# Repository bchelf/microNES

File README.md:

# microNES

`microNES` is a small RP2350-based NES emulator project with custom hardware,
portable emulator code, and host-side development tools.

The repo now includes a complete KiCad implementation of an RP2350 console-style
board, plus firmware for composite video, HDMI output, SD-card ROM loading,
controller input, and audio. It also includes host tools for building, running,
capturing, and validating the same emulator core on a desktop.

ROM images are not included.

## What This Repo Does

- Runs NES ROMs through a shared C emulator core.
- Targets RP2350 / Raspberry Pi Pico 2-class hardware.
- Provides a fully functional KiCad PCB design under `hardware/microNES_pcb_v0.1`.
- Outputs analog composite video from the RP2350 using PIO/DMA timing.
- Outputs HDMI/DVI-style video using the RP2350 HSTX path.
- Loads ROMs at runtime from SD card, with an optional flash/XIP cache.
- Supports NES controller input.
- Produces audio through PWM on the Pico targets, with a MAX98357 I2S path for
  the TFT audio target.
- Builds host tools for smoke tests, SDL play, PNG frame dumps, WAV dumps, and
  ffmpeg video capture.
- Includes an ESP32-S3 frontend as a separate reference platform.
- Includes an Emscripten/WebAssembly target stub for browser experiments.

## Current Status

The project has moved beyond the original SMB1-only bring-up. The core still
prioritizes pragmatic compatibility over perfect NES accuracy, but the repo now
contains support for several common mapper families:

- NROM / mapper 0
- MMC1
- UxROM
- CNROM
- AxROM
- GxROM
- Color Dreams
- MMC2
- MMC3
- mapper 40

The hardware and firmware path is centered on the RP2350 board in
`hardware/microNES_pcb_v0.1`, with composite and HDMI firmware targets in
`src/pico`. The host path remains the fastest way to validate emulator behavior
before testing on hardware.

## Hardware

The KiCad project lives here:

```text
hardware/microNES_pcb_v0.1/
```

It includes:

- KiCad schematic and PCB files
- custom symbols and footprints
- RP2350 QFN footprint and 3D model support
- microSD slot support
- USB-C support
- NES controller connector footprint
- custom KiCad footprints for original Nintendo console parts
- composite output hardware
- production outputs, BOM, placement files, and Gerbers

The board is designed around harvested original NES console hardware for the
user-facing controls and controller interface. It uses the original Nintendo
power switch assembly and original NES controller input ports, with custom KiCad
footprints made specifically for those salvaged parts.

The older breadboard composite schematic is documented in `SCHEMATIC.md`. The
PCB target is selected in firmware with:

```sh
-DMICRONES_BOARD=v0_1
```

## Repo Layout

```text
src/common/      Portable emulator core, ROM menu, mappers, CPU, PPU, APU, input
src/host/        Desktop smoke runner, SDL runner, PNG/WAV/video tooling
src/pico/        RP2350 firmware, composite, HDMI, TFT, SD, flash cache, audio
src/esp32s3/     Separate ESP32-S3 frontend/reference implementation
src/web/         Emscripten/WebAssembly browser frontend
hardware/        KiCad PCB design, production files, Gerbers, BOMs
tests/           Emulator test ROMs and menu smoke tests
```

## Build

### Host

```sh
cmake -S . -B build-host -DMICRONES_PLATFORM=host
cmake --build build-host -j
```

This builds:

- `build-host/micrones_smoke`
- `build-host/micrones_menu_smoke`
- `build-host/micrones` when SDL3 is available

Run a ROM locally:

```sh
./build-host/micrones roms/smb1.nes
```

Run deterministic smoke validation:

```sh
./build-host/micrones_smoke roms/smb1.nes
```

Capture a frame or video:

```sh
./build-host/micrones_smoke roms/smb1.nes 6200000 /tmp/micrones_10s.png
./build-host/micrones_smoke roms/smb1.nes --steps 17670500 --video-out build-host/capture.mp4
```

### RP2350 / Pico

Configure the firmware for the emulator and the custom PCB:

```sh
cmake -S . -B build-pico \
  -DMICRONES_PLATFORM=pico \
  -DMICRONES_PICO_VIDEO_MODE=emulator \
  -DMICRONES_BOARD=v0_1 \
  -Dpicotool_DIR=/Users/bchelf/microNES/build/_deps/picotool
```

Build composite output:

```sh
cmake --build build-pico --target micrones_pico_analog -j
```

Build HDMI output:

```sh
cmake --build build-pico --target micrones_pico_hdmi -j
```

Other firmware targets:

```sh
cmake --build build-pico --target micrones_pico_tft -j
cmake --build build-pico --target micrones_pico_tft_max98357 -j
cmake --build build-pico --target micrones_pico_hdmi_test_pattern -j
```

The Pico firmware loads ROMs from SD at runtime. `MICRONES_PICO_ROM_PATH` is no
longer needed for normal Pico builds.

### Web

```sh
emcmake cmake -S . -B build-web -DMICRONES_PLATFORM=web
cmake --build build-web -j
```

The build copies `src/web/index.html` next to the generated JS/WASM output.

### ESP32-S3

```sh
cd src/esp32s3
. $IDF_PATH/export.sh
idf.py build
```

## Host Controls

For the SDL runner:

- Arrow keys or `WASD`: D-pad
- `L`: A
- `K`: B
- `Return`: Start
- `Tab` or right shift: Select

Useful runner options:

```sh
./build-host/micrones roms/smb1.nes --vsync
./build-host/micrones roms/smb1.nes --no-vsync --unthrottled
./build-host/micrones roms/smb1.nes --scale 5
./build-host/micrones roms/smb1.nes --dump-wav /tmp/gameplay.wav --dump-wav-seconds 2
```

## Known Limitations

`microNES` is still an emulator under active development, not a fully accurate
general-purpose NES implementation.

- PPU timing is practical rather than fully cycle-accurate.
- Sprite overflow and exact secondary OAM behavior are incomplete.
- APU fidelity is improved but still not perfect.
- Mapper support exists for several common boards, but compatibility is not
  expected to match mature NES emulators.
- Some RP2350 SD-to-flash-cache ROM load paths can still disturb video output
  and are an active debugging area.

## Development Notes

Keep platform boundaries clean:

- `src/common` should stay portable.
- Host-only SDL, PNG, WAV, and ffmpeg code belongs in `src/host`.
- Pico SDK, PIO, DMA, HSTX, SD, and flash code belongs in `src/pico`.
- ESP-IDF code belongs in `src/esp32s3`.

The recommended workflow is still host-first: validate behavior with
`micrones_smoke` and the SDL runner, then test the same core on RP2350 hardware.

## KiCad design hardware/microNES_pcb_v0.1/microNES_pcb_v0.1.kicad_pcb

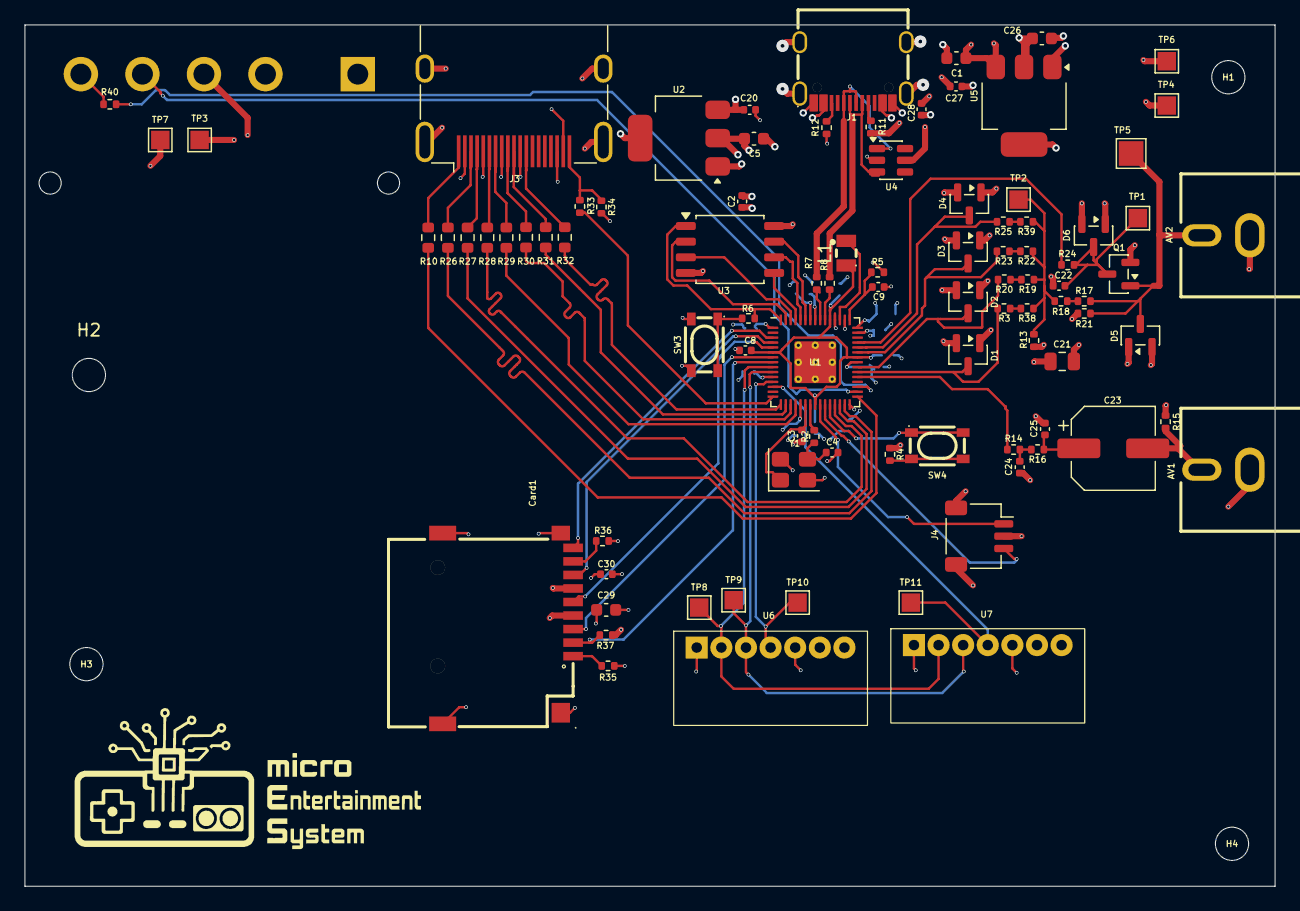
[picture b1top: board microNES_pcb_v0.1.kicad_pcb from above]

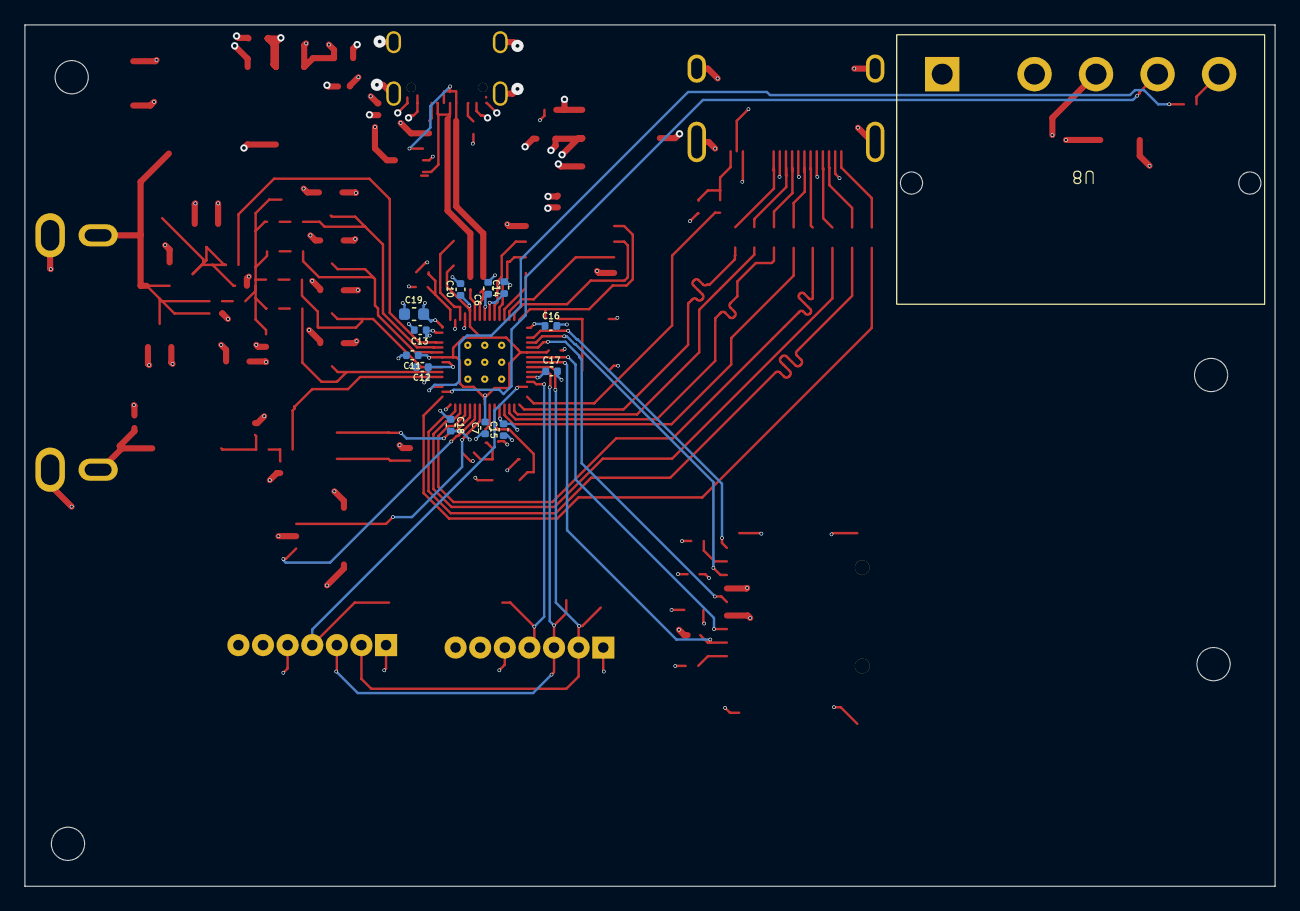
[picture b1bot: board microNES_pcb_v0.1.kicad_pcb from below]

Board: 4 copper layers, 101.6 x 70.0 mm, 108 parts (13 on the bottom side), 77 nets.

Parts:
AV1, AV2: AV-5; CONN-TH_AV-5
C1, C5, C19, C26, C29: 10uF; C_0603_1608Metric
C2, C8, C11, C12, C13, C14, C15, C16, C17, C18, C20, C27, C28, C30: 100nF; C_0402_1005Metric
C3, C4: 15pF; C_0402_1005Metric
C6, C7, C9, C10: 4.7uF; C_0402_1005Metric
C21: 100nF; C_0805_2012Metric
C22, C24, C25: 10nF; C_0402_1005Metric
C23: 100uF; CP_Elec_6.3x5.4
Card1: TF PUSH; TF-SMD_TF-PUSH
D1, D2, D3, D4, D5, D6: BAT54S; SOT-23
H1, H2, H3, H4: MountingHole; MountingHole_2.7mm_M2.5
J1: USB_C_Receptacle_USB2.0_16P; USB-C_SMD-TYPE-C-31-M-12_1
J3: HDMI_E; HDMI_A_Molex_208658-1001_Horizontal
J4: SM03B-SRSS-TB; JST_SH_SM03B-SRSS-TB_1x03-1MP_P1.00mm_Horizontal
L1: 3.3uH; IND-SMD_L2.0-W1.6_AOTA-B201610S3R3-101-T
Q1: 2N7002; SOT-23
R2, R3, R4, R6, R14, R16: 1k; R_0402_1005Metric
R5: 33; R_0402_1005Metric
R7, R8: 27; R_0402_1005Metric
R10, R26, R27, R28, R29, R30, R31, R32: 270; R_0603_1608Metric
R11, R12: 5.1k; R_0402_1005Metric
R13, R40: 330; R_0402_1005Metric
R15, R21, R33, R35, R36, R37: 10k; R_0402_1005Metric
R17: 7.5; R_0402_1005Metric
R18: 68; R_0402_1005Metric
R19: 15; R_0402_1005Metric
R20: 470; R_0402_1005Metric
R22: 22; R_0402_1005Metric
R23: 220; R_0402_1005Metric
R24: 100; R_0402_1005Metric
R25: 120; R_0402_1005Metric
R34: 20k; R_0402_1005Metric
R38, R39: 0; R_0402_1005Metric
SW3, SW4: PTS810SJM250SMTRLFS; KEY-SMD_4P-L4.2-W3.2-P2.20-LS4.6
TP1: TestPoint; TestPoint_Pad_1.5x1.5mm
TP2, TP3, TP4, TP6, TP7, TP8, TP9, TP10, TP11: TestPoint_Pad_1.5x1.5mm
TP5: TestPoint; TestPoint_Pad_2.0x2.0mm
U1: RP2350_60QFN; RP2350-QFN-60-1EP_7x7_P0.4mm_EP3.4x3.4mm_ThermalVias
U2, U5: AMS1117-3.3; SOT-223-3_TabPin2
U3: W25Q128JVS; SOIC-8_5.3x5.3mm_P1.27mm
U4: SOT-23-6
U6, U7: NES_1x7_CustomPitch
U8: NES_Power_Reset_LED_5pin
Y1: ABM8-272-T3; Crystal_SMD_3225-4Pin_3.2x2.5mm

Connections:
+1V1: C7.1, C8.1, C10.1, C11.1, L1.1, U1.6 (DVDD), U1.23 (DVDD), U1.39 (DVDD), U1.50 (VREG_FB)
+3.3VDAC: C21.1, C26.1, D1.2 (K), D2.2 (K), D3.2 (K), D4.2 (K), D5.2 (K), D6.2 (K), R13.1, TP6.1 (1_1), U5.2 (VO)
+3V3: C2.1, C5.1, C6.1, C12.1, C13.1, C14.1, C15.1, C16.1, C17.1, C18.1, C19.1, C29.1, C30.1, Card1.4 (VDD), R5.1, R35.1, R36.1, R37.1, TP3.1 (1_1), U1.1 (IOVDD), U1.11 (IOVDD), U1.20 (IOVDD), U1.30 (IOVDD), U1.38 (IOVDD), U1.44 (ADC_AVDD), U1.45 (IOVDD), U1.49 (VREG_VIN), U1.53 (USB_OTP_VDD), U1.54 (QSPI_IOVDD), U2.2 (VO), U3.8 (VCC), U6.5 (VCC), U7.5 (VCC), U8.3 (RST_VCC)
/ADAC_OUT: AV1.2, C23.2, R15.1
/AUD_A: C24.1, R14.2, R16.1
/AUD_B: C23.1, C25.1, R16.2
/CARD_CD: Card1.CD, U1.3 (GPIO1)
/CARD_CD_DAT3: Card1.2 (CD/DAT3), R37.2, U1.8 (GPIO5)
/CARD_CLX: Card1.5 (CLX), U1.5 (GPIO3)
/CARD_CMD: Card1.3 (CMD), U1.7 (GPIO4)
/CARD_DAT0: Card1.7 (DAT0), U1.4 (GPIO2)
/GATE_NODE: C22.1, D6.3 (COM), Q1.3 (D), R24.1, TP1.1 (1_1)
/GPIO12: R32.1, U1.16 (GPIO12)
/GPIO13: R31.1, U1.17 (GPIO13)
/GPIO14: R30.1, U1.18 (GPIO14)
/GPIO15: R29.1, U1.19 (GPIO15)
/GPIO16: R28.1, U1.27 (GPIO16)
/GPIO17: R27.1, U1.28 (GPIO17)
/GPIO18: R26.1, U1.29 (GPIO18)
/GPIO19: R10.1, U1.31 (GPIO19)
/GP_ADAC_IN: R14.1, U1.35 (GPIO23)
/GP_VDAC_GATE: R24.2, U1.42 (GPIO28_ADC2)
/GP_VDAC_SUM0: D1.3 (COM), R3.2, U1.36 (GPIO24)
/GP_VDAC_SUM1: D2.3 (COM), R20.2, U1.37 (GPIO25)
/GP_VDAC_SUM2: D3.3 (COM), R23.2, U1.40 (GPIO26_ADC0)
/GP_VDAC_SUM3: D4.3 (COM), R25.2, U1.41 (GPIO27_ADC1)
/HDMI_HPD: R33.2, U1.15 (GPIO11)
/NES_CLOCK: TP8.1 (1_1), U1.9 (GPIO6), U6.2 (CLOCK), U7.2 (CLOCK)
/NES_DATA_1: TP10.1 (1_1), U1.12 (GPIO8), U6.4 (DATA)
/NES_DATA_2: TP11.1 (1_1), U1.13 (GPIO9), U7.4 (DATA)
/NES_LATCH: TP9.1 (1_1), U1.10 (GPIO7), U6.3 (LATCH), U7.3 (LATCH)
/PWR_LED: R40.2, U1.33 (GPIO21)
/QSPI_SCLK: U1.56 (QSPI_SCLK), U3.6 (CLK)
/QSPI_SD0: U1.57 (QSPI_SD0), U3.5 (DI(IO0))
/QSPI_SD1: U1.59 (QSPI_SD1), U3.2 (DO(IO1))
/QSPI_SD2: U1.58 (QSPI_SD2), U3.3 (IO2)
/QSPI_SD3: U1.55 (QSPI_SD3), U3.7 (IO3)
/QSPI_SS: R6.1, U1.60 (QSPI_SS), U3.1 (~CS)
/RST_BTN: U1.32 (GPIO20), U8.4 (RST_OUT)
/RUN: SW4.1, SW4.2, U1.26 (RUN)
/SUM_NODE: R13.2, R18.2, R19.1, R22.1, R38.2, R39.2, TP2.1 (1_1)
/SWCLK: J4.1, U1.24 (SWCLK)
/SWD: J4.3, U1.25 (SWD)
/USB_D+: J1.A6 (DP1), J1.B6 (DP2), R7.1, U4.1 (IO1)
/USB_D-: J1.A7 (DN1), J1.B7 (DN2), R8.1, U4.3 (IO2)
/VBUS_RAW: J1.A4B9 (VBUS), J1.B4A9 (VBUS), U8.1 (PWR_SW_A)
/VDAC_OUT: AV2.2, D5.3 (COM), Q1.1 (G), R17.1, R21.2, TP5.1 (1_1)
/VREG_AVDD: C9.1, R5.2, U1.46 (VREG_AVDD)
/VREG_LX: L1.2, U1.48 (VREG_LX)
/XIN: C3.1, U1.21 (XIN), Y1.1
/XOUT: R2.1, U1.22 (XOUT)
/~USB_BOOT: R6.2, SW3.1, SW3.2
GND: AV1.1, AV2.1, C1.1, C2.2, C3.2, C4.2, C5.2, C6.2, C7.2, C8.2, C9.2, C10.2, C11.2, C12.2, C13.2, C14.2, C15.2, C16.2, C17.2, C18.2, C19.2, C20.1, C21.2, C22.2, C24.2, C25.2, C26.2, C27.1, C28.1, C29.2, C30.2, Card1.6 (VSS), Card1.10, Card1.11, Card1.12, Card1.13, D1.1 (A), D2.1 (A), D3.1 (A), D4.1 (A), D5.1 (A), D6.1 (A), J1.1 (EH), J1.2 (EH), J1.3 (EH), J1.4 (EH), J1.A1B12 (GND), J1.B1A12 (GND), J3.2 (D2S), J3.5 (D1S), J3.8 (D0S), J3.11 (CKS), J3.17 (GND), J3.SH, J4.2, J4.MP (MountPin), Q1.2 (S), R4.2, R11.1, R12.2, R15.2, R21.1, R34.2, SW3.3, SW3.4, TP4.1 (1_1), TP7.1 (1_1), U1.47 (VREG_PGND), U1.61 (GND), U2.1 (GND), U3.4 (GND), U4.2 (GND), U5.1 (GND), U6.1 (GND), U7.1 (GND), Y1.2, Y1.4
unnamed: C4.1, R2.2, Y1.3
unnamed: Card1.8 (DAT1), R36.2
unnamed: Card1.1 (DAT2), R35.2
unnamed: J1.A5 (CC1), R11.2
unnamed: J1.B5 (CC2), R12.1
unnamed: J3.10 (CK+), R31.2
unnamed: J3.12 (CK-), R32.2
unnamed: J3.7 (D0+), R29.2
unnamed: J3.9 (D0-), R30.2
unnamed: J3.4 (D1+), R27.2
unnamed: J3.6 (D1-), R28.2
unnamed: J3.1 (D2+), R10.2
unnamed: J3.3 (D2-), R26.2
unnamed: J3.19 (HPD), R33.1, R34.1
unnamed: R3.1, R38.1
unnamed: R4.1, SW4.3, SW4.4
unnamed: R17.2, R18.1
unnamed: R19.2, R20.1
unnamed: R22.2, R23.1
unnamed: R25.1, R39.1
unnamed: R8.2, U1.51 (USB_DM)
unnamed: R7.2, U1.52 (USB_DP)
unnamed: R40.1, U8.5 (LED_K)
VBUS: C1.2, C20.2, C27.2, C28.2, J3.18 (+5V), U2.3 (VI), U4.5 (VBUS), U5.3 (VI), U8.2 (PWR_SW_B)

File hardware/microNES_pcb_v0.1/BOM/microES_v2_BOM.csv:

Comment,Designator,Footprint,JLCPCB Part #
AV-5,"AV1,AV2",microNES_footprints:CONN-TH_AV-5,C18080
10uF,"C1,C5,C19,C26,C29",Capacitor_SMD:C_0603_1608Metric,C19702
100nF,"C2,C8,C11,C12,C13,C14,C15,C16,C17,C18,C20,C27,C28,C30",Capacitor_SMD:C_0402_1005Metric,C307331
15pF,"C3,C4",Capacitor_SMD:C_0402_1005Metric,C1548
4.7uF,"C6,C7,C9,C10",Capacitor_SMD:C_0402_1005Metric,C23733
100nF,C21,Capacitor_SMD:C_0805_2012Metric,C49678
10nF,"C22,C24,C25",Capacitor_SMD:C_0402_1005Metric,C15195
100uF,C23,Capacitor_SMD:CP_Elec_6.3x5.4,C29179
TF PUSH,Card1,microNES_footprints:TF-SMD_TF-PUSH,C393941
BAT54S,"D1,D2,D3,D4,D5,D6",Package_TO_SOT_SMD:SOT-23,C47546
USB_C_Receptacle_USB2.0_16P,J1,microNES_footprints:USB-C_SMD-TYPE-C-31-M-12_1,C165948
HDMI_E,J3,Connector_Video:HDMI_A_Molex_208658-1001_Horizontal,C2962407
SM03B-SRSS-TB,J4,Connector_JST:JST_SH_SM03B-SRSS-TB_1x03-1MP_P1.00mm_Horizontal,C160403
3.3uH,L1,microNES_footprints:IND-SMD_L2.0-W1.6_AOTA-B201610S3R3-101-T,C42411119
2N7002,Q1,Package_TO_SOT_SMD:SOT-23,C8545
1k,"R2,R3,R4,R6,R14,R16",Resistor_SMD:R_0402_1005Metric,C11702
33,R5,Resistor_SMD:R_0402_1005Metric,C25105
27,"R7,R8",Resistor_SMD:R_0402_1005Metric,C25100
270,"R10,R26,R27,R28,R29,R30,R31,R32",Resistor_SMD:R_0603_1608Metric,C22966
5.1k,"R11,R12",Resistor_SMD:R_0402_1005Metric,C25905
330,"R13,R40",Resistor_SMD:R_0402_1005Metric,C25104
10k,"R15,R21,R33,R35,R36,R37",Resistor_SMD:R_0402_1005Metric,C2765610
7.5,R17,Resistor_SMD:R_0402_1005Metric,C47764
68,R18,Resistor_SMD:R_0402_1005Metric,C25131
15,R19,Resistor_SMD:R_0402_1005Metric,C25083
470,R20,Resistor_SMD:R_0402_1005Metric,C25117
22,R22,Resistor_SMD:R_0402_1005Metric,C25092
220,R23,Resistor_SMD:R_0402_1005Metric,C25091
100,R24,Resistor_SMD:R_0402_1005Metric,C2784782
120,R25,Resistor_SMD:R_0402_1005Metric,C25079
20k,R34,Resistor_SMD:R_0402_1005Metric,C25765
0,"R38,R39",Resistor_SMD:R_0402_1005Metric,C17168
PTS810SJM250SMTRLFS,"SW3,SW4",microNES_footprints:KEY-SMD_4P-L4.2-W3.2-P2.20-LS4.6,C116501
RP2350_60QFN,U1,microNES_footprints:RP2350-QFN-60-1EP_7x7_P0.4mm_EP3.4x3.4mm_ThermalVias,C42411118
AMS1117-3.3,"U2,U5",Package_TO_SOT_SMD:SOT-223-3_TabPin2,C6186
W25Q128JVS,U3,Package_SO:SOIC-8_5.3x5.3mm_P1.27mm,C97521
,U4,Package_TO_SOT_SMD:SOT-23-6,C7519
ABM8-272-T3,Y1,Crystal:Crystal_SMD_3225-4Pin_3.2x2.5mm,C20625731

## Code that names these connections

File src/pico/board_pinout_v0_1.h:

#ifndef MICRONES_BOARD_PINOUT_V0_1_H
#define MICRONES_BOARD_PINOUT_V0_1_H

/*
 * microNES PCB v0.1 — canonical RP2350 GPIO pinout.
 *
 * Source of truth: hardware/microNES_pcb_v0.1/microNES_pcb_v0.1.kicad_sch
 * (U1, RP2350_60QFN, placed at (240.03, 105.41) in the schematic).
 *
 * The schematic uses local labels on each RP2350 GPIO pin.  This header
 * mirrors those labels exactly, so a build configured with
 * -DMICRONES_BOARD=v0_1 (or by defining MICRONES_BOARD_V0_1 in CMake) drives
 * the same nets the PCB silkscreen names.
 *
 *   Schematic label  | GPIO | Peripheral / function
 *   -----------------|------|-------------------------------------------
 *   GPIO0            |  0   | unused / test point
 *   CARD_CD          |  1   | SD card detect (active-low input)
 *   CARD_DAT0        |  2   | SD card DAT0  / SPI MISO (PIO-SPI)
 *   CARD_CLX         |  3   | SD card CLK   / SPI SCK  (PIO-SPI)
 *   CARD_CMD         |  4   | SD card CMD   / SPI MOSI (PIO-SPI)
 *   CARD_CD_DAT3     |  5   | SD card DAT3  / SPI CS   (PIO-SPI)
 *   NES_CLOCK        |  6   | NES 4021 controller CLOCK (output)
 *   NES_LATCH        |  7   | NES 4021 controller LATCH (output)
 *   NES_DATA_1       |  8   | NES controller #1 DATA (input, pull-up)
 *   NES_DATA_2       |  9   | NES controller #2 DATA (input, pull-up)
 *   (unused)         | 10   | -
 *   HDMI_HPD         | 11   | HDMI hot-plug detect (input)
 *   (header)         | 12   | exposed via expansion header (no on-board fn)
 *   (header)         | 13   | exposed via expansion header
 *   (header)         | 14   | exposed via expansion header
 *   (header)         | 15   | exposed via expansion header
 *   (header)         | 16   | exposed via expansion header
 *   (header)         | 17   | exposed via expansion header
 *   (header)         | 18   | exposed via expansion header
 *   (header)         | 19   | exposed via expansion header
 *   RST_BTN          | 20   | reset / user button (input, pull-up)
 *   PWR_LED          | 21   | power LED (output, active-high)
 *   (unused)         | 22   | -
 *   GP_ADAC_IN       | 23   | audio DAC PWM input (drives ADAC_OUT chain)
 *   GP_VDAC_SUM0     | 24   | composite video DAC bit 0 (LSB, 1000 Ω)
 *   GP_VDAC_SUM1     | 25   | composite video DAC bit 1 (485 Ω)
 *   GP_VDAC_SUM2     | 26   | composite video DAC bit 2 (242 Ω)
 *   GP_VDAC_SUM3     | 27   | composite video DAC bit 3 (MSB, 120 Ω)
 *   GP_VDAC_GATE     | 28   | sync-clamp N-MOSFET gate (active-high)
 *   (unused)         | 29   | -
 *
 * Notes on consequences of this pinout:
 *
 * - The composite video DAC occupies GP24..GP27, a contiguous 4-pin block,
 *   so the existing PIO program (`out pins, 4`) still works unchanged —
 *   only MICRONES_VIDEO_PIN_BASE needs to change from 10 to 24.
 *
 * - The sync clamp (GP_VDAC_GATE) is GP28, a plain GPIO toggled by CPU.
 *
 * - Audio uses PWM on GP23 → external analog DAC / filter chain
 *   (ADAC_OUT → AUD_A/AUD_B line outputs).  The MAX98357 I2S backend is
 *   NOT present on the v0.1 PCB; that backend remains targeted at
 *   breadboard rigs and is unaffected by this header.
 *
 * - The SD card slot uses GP1..GP5 with non-standard signal ordering
 *   (CD, DAT0, CLK, CMD, DAT3).  This cannot reach the RP2350 hardware
 *   SPI peripheral's IO mux, so the SD driver runs SPI through PIO; that
 *   was already true in `sd_card_pins.h` and matches this layout.
 *
 * - The NES controller block uses GP6..GP9 (vs. GP18..GP20 on breadboard).
 *   The PCB exposes a second-player DATA line on GP9 (NES_DATA_2); the
 *   existing single-controller firmware ignores it.
 */

/* --- Composite NTSC video DAC ---------------------------------------------- */
#define MICRONES_V0_1_PIN_VDAC_BIT0     24u  /* GP_VDAC_SUM0, LSB */
#define MICRONES_V0_1_PIN_VDAC_BIT1     25u  /* GP_VDAC_SUM1 */
#define MICRONES_V0_1_PIN_VDAC_BIT2     26u  /* GP_VDAC_SUM2 */
#define MICRONES_V0_1_PIN_VDAC_BIT3     27u  /* GP_VDAC_SUM3, MSB */
#define MICRONES_V0_1_PIN_VDAC_BASE     MICRONES_V0_1_PIN_VDAC_BIT0
#define MICRONES_V0_1_PIN_VDAC_GATE     28u  /* GP_VDAC_GATE, sync-clamp MOSFET */

/* --- Audio PWM (drives external ADAC / analog filter) --------------------- */
#define MICRONES_V0_1_PIN_AUDIO_PWM     23u  /* GP_ADAC_IN */

/* --- NES controller (4021 PISO shift register) ---------------------------- */
#define MICRONES_V0_1_PIN_NES_CLOCK     6u   /* NES_CLOCK,  output */
#define MICRONES_V0_1_PIN_NES_LATCH     7u   /* NES_LATCH,  output */
#define MICRONES_V0_1_PIN_NES_DATA      8u   /* NES_DATA_1, input, pull-up */
#define MICRONES_V0_1_PIN_NES_DATA_P2   9u   /* NES_DATA_2, input, pull-up (second player) */

/* --- SD card (PIO-SPI) ---------------------------------------------------- */
#define MICRONES_V0_1_PIN_SD_CD         1u   /* CARD_CD,       card-detect */
#define MICRONES_V0_1_PIN_SD_MISO       2u   /* CARD_DAT0,     SPI MISO */
#define MICRONES_V0_1_PIN_SD_SCK        3u   /* CARD_CLX,      SPI SCK  */
#define MICRONES_V0_1_PIN_SD_MOSI       4u   /* CARD_CMD,      SPI MOSI */
#define MICRONES_V0_1_PIN_SD_CS         5u   /* CARD_CD_DAT3,  SPI CS   */

/* --- Other on-board peripherals ------------------------------------------- */
#define MICRONES_V0_1_PIN_HDMI_HPD      11u  /* HDMI hot-plug detect (input) */
#define MICRONES_V0_1_PIN_RST_BUTTON    20u  /* user/reset button (input)    */
#define MICRONES_V0_1_PIN_PWR_LED       21u  /* power LED (output)           */

#endif /* MICRONES_BOARD_PINOUT_V0_1_H */

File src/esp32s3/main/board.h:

#pragma once

// ============================================================
// GPIO pin definitions for Waveshare ESP32-S3-Touch-AMOLED-1.91
// Verify against your specific board revision's schematic.
// ============================================================

// --- QSPI Display (SH8601 AMOLED) ---
// Pin assignments from official Waveshare schematic
#define BOARD_LCD_QSPI_CS     6   // QSPI chip select
#define BOARD_LCD_QSPI_SCLK  47   // QSPI clock
#define BOARD_LCD_QSPI_D0    18   // QSPI D0
#define BOARD_LCD_QSPI_D1     7   // QSPI D1
#define BOARD_LCD_QSPI_D2    48   // QSPI D2
#define BOARD_LCD_QSPI_D3     5   // QSPI D3
#define BOARD_LCD_RST        17   // AMOLED reset (active low)
#define BOARD_LCD_TE         16   // Tearing-effect pin (NC by default)

// --- I2C bus (shared by Touch + IMU) ---
#define BOARD_I2C_PORT        0   // I2C peripheral number
#define BOARD_I2C_SDA        40   // GP40 per board pinout
#define BOARD_I2C_SCL        39   // GP39 per board pinout
#define BOARD_I2C_FREQ_HZ   400000

// --- Touch controller (FT3168) ---
#define BOARD_TP_I2C_ADDR  0x38   // 7-bit I2C address
#define BOARD_TP_RST         17   // Shared with AMOLED reset (GPIO17)
#define BOARD_TP_INT         41   // TP interrupt pin

// --- IMU (QMI8658) – same I2C bus, not used by emulator ---
#define BOARD_IMU_I2C_ADDR 0x6B   // AD0 pulled high; use 0x6A if AD0 low

// --- Audio output (MAX98357A I2S amplifier) ---
// Wire MAX98357A:  BCLK→GPIO4, LRC→GPIO2, DIN→GPIO3
//                 VIN→3.3V (or 5V for more volume), GND→GND
//                 SD_MODE→leave unconnected ((L+R)/2 mix, best for mono speaker)
//                 OUT+/OUT- directly to 8-ohm speaker
#define BOARD_AUDIO_I2S_PORT   I2S_NUM_0
#define BOARD_AUDIO_BCLK_PIN   4
#define BOARD_AUDIO_WS_PIN     2
#define BOARD_AUDIO_DOUT_PIN   3

// --- NES hardware controller (original 4021 PISO shift register) ---
// Connect the 7-pin NES controller cable as follows:
//   NES pin 1 (VCC)   → 3.3 V
//   NES pin 2 (CLOCK) → GPIO 11 (output from ESP32-S3)
//   NES pin 3 (LATCH) → GPIO 12 (output from ESP32-S3)
//   NES pin 4 (DATA)  → GPIO 13 (input to ESP32-S3; pull-up enabled in firmware)
//   NES pin 7 (GND)   → GND
// Pins 5 and 6 are not connected on a standard NES controller.
#define BOARD_NES_CTL_CLOCK  11
#define BOARD_NES_CTL_LATCH  12
#define BOARD_NES_CTL_DATA   13

// --- Power / battery ADC ---
#define BOARD_BAT_ADC_CHANNEL  ADC_CHANNEL_0   // GPIO1

// ============================================================
// Display geometry
// ============================================================

// Native portrait resolution
#define BOARD_LCD_NATIVE_W   240
#define BOARD_LCD_NATIVE_H   536

// After 90° CW rotation (landscape) used for NES layout
#define DISPLAY_W            536   // landscape width  = native height
#define DISPLAY_H            240   // landscape height = native width

// NES framebuffer: 256×240, placed in the centre of the landscape display
//   left zone  [  0 .. 139] × [0 .. 239]  – D-pad
//   NES region [140 .. 395] × [0 .. 239]  – emulator output
//   right zone [396 .. 535] × [0 .. 239]  – A/B/Start/Select
#define NES_DISPLAY_X        140
#define NES_DISPLAY_Y          0
#define NES_DISPLAY_W        256   // == NES_FRAME_WIDTH
#define NES_DISPLAY_H        240   // == NES_FRAME_HEIGHT

#define UI_LEFT_X              0
#define UI_LEFT_W            140
#define UI_RIGHT_X           396
#define UI_RIGHT_W           140

// SPI bus configuration
#define BOARD_LCD_SPI_HOST   SPI2_HOST
#define BOARD_LCD_SPI_CLK_HZ (80 * 1000 * 1000)  // 80 MHz – RM67162 QSPI max

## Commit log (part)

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2026-03-24 deploy: dbb2e23832906f3fbe98563b655aeb6c592fd55a
2026-03-24 Change ESP32-S3 NES controller pins from GPIO 8/9/10 to GPIO 11/12/13
    GPIO 11 (CLOCK), 12 (LATCH), 13 (DATA) are broken out on the board.
    All three remain free of conflicts with the display (5–7, 16–18, 47–48),
    I2C/touch (17, 39–41), audio (46), and battery ADC (1).
    https://claude.ai/code/session_01GDkdEC1fHSnBSoEC1kJ4Ad
2026-03-25 deploy: 44193075bb9132fedaf451e7e4728d7438745fac
2026-03-26 Fix reset button: rename menu to RESET with NES-style styling
    Move the reset button from the A/B section into the center column,
    centered above SELECT and START. Style it as a gray rectangular
    button with a 3D raised look matching the original NES console Reset
    button aesthetic.
    https://claude.ai/code/session_01UYTpprx3jk8CpmVNhBdGoT
2026-03-26 deploy: 0939bfe64bd9c0a77e30cff0f0a52a2ef0b51d74
2026-03-26 Fix board.h comment: SD_MODE should be left floating for mono (L+R)/2 mix
    https://claude.ai/code/session_01JjeufyMtXL1UZYcH2dKqeQ
2026-03-26 Add per-step timing instrumentation to emulator loop
    Measures µs spent in touch_read, nes_step_frame, and audio drain
    separately, averaged over each 60-frame diagnostic window. Printed
    alongside fps/audio stats to identify the 19ms/frame bottleneck.
    https://claude.ai/code/session_01DnRzgC7KR6qjsRyBH4U67A
2026-03-26 feat: reduce audio output volume to 75%
    Scale PCM samples by 3/4 before pushing to audio buffer.
    https://claude.ai/code/session_01DnRzgC7KR6qjsRyBH4U67A
2026-03-26 chore: ignore build_* directories in .gitignore
    The host smoke build produces build_host/ which wasn't covered by the
    existing build-*/ pattern. Add build_*/ to catch all underscore-prefixed
    build directories.
    https://claude.ai/code/session_01DnRzgC7KR6qjsRyBH4U67A
2026-03-27 Revert "perf: restore flatten on cpu6502_run_scanline via optimize("Os")"
    This reverts commit bc738a7f83b31dd868f7be6a2ca90d8fecdd1e82.
2026-03-30 fix to 315
2026-03-31 deploy: 20e0cc2cb4218ad23a46af59fec86d07f29e44cb
2026-04-01 docs: add CLAUDE.md with recent APU DMC fix notes
    Documents the DMC emulation improvements made in this session:
    rate table fix, DMA sample buffer, delta output, and scanline-path
    DMA calls. Summarises AccuracyCoin p14 before/after results and
    lists known remaining gaps that require cycle-accurate emulation.
    https://claude.ai/code/session_01HMGj1ooHrmfoty5u7xyPyV
2026-04-07 Add 8-bit parallel 8080 TFT backend (ILI9486/ILI9488, ~60fps) (#18)
    * add parallel TFT support
    * remove intro test delay
    ---------
2026-04-14 Revert chroma phase offset, keep amplitude at 3.5
    The +π phase correction made colors worse in practice. Removed it,
    keeping only the amplitude increase from 2.5 to 3.5.
    https://claude.ai/code/session_01U5noarKvnVk15q5vPh9uSZ
2026-04-14 Add left/right blank borders to centre 256 NES pixels in active region
    The 758-sample active video region is correct for NTSC timing, but the
    NES pixel clock (5.3693 MHz) only fills ~683 samples for 256 pixels.
    Previously all 256 pixels were stretched across 758 samples, making the
    image ~11% too wide and pushing edges into TV overscan.
    Now: 37 blank samples left + 683 pixel samples + 38 blank samples right
    = 758 total. Subcarrier phase adjusted for the border offset.
2026-04-15 Improve documentation for NTSC color encoding tables
    Add top-level overview comment explaining how the three cooperating
    tables (burst pattern, chroma LUT, row scaling) work together.
    Expand inline comments for precompute_palette, chroma_lut, and
    per-row scaling with rationale and NES palette index bit layout.
    https://claude.ai/code/session_01U5noarKvnVk15q5vPh9uSZ
2026-04-17 deploy: d077d4b37d13f99d5918776ea1ca415cde44cace
2026-04-25 fix up some things
2026-05-08 deploy: 6474ec50df785d372a1bf5b9d8526ad7b2612bc7
2026-05-09 Add per-step diagnostic logging inside sd_init()
    When init fails the operator now sees exactly where: the warmup byte
    stream off MISO (FF/00/garbage tells us pullup vs swap vs floating
    clock), the R1 byte from each CMD0 attempt, plus the resolved pin
    numbers and PIO index. Cheap — runs once at boot, gated on
    MICRONES_SD_INIT_DEBUG (defaults to 1; can be -D'd off later).
2026-05-10 Switch SD-card driver to hardware SPI peripheral
    Diagnostic branch. PIO has been verified working but the card still
    won't init through the HW-125 breakout. This branch reverts the SD
    bit pump to the RP2350 hardware SPI peripheral (spi_init,
    spi_write_read_blocking) so we can rule out PIO-specific subtleties
    (setup/hold timing, drive strength, bit alignment, ...).
    Pin defaults moved to a silicon-correct SPI0 set on the upper bank:
2026-05-10 Slow controller bus to original NES spec (12/6 us)
    Was 6/2 us (latch / clock half-period). Bench-tested fine but
    proved marginal on breadboard wiring — the 4021 would shift bit 0
    and bit 1 cleanly then DATA would latch low for the rest of the
    read, leaving D-pad / Start / Select dead and A or B alone reading
    as 'all buttons pressed.'
    Bumping to 12 us latch and 6 us clock half-period (12 us full
2026-05-11 codex fixes
2026-05-18 Pico: revert v0.1 video DAC to 4 mA, keep fast slew
    The earlier 12 mA + fast-slew bump made the test pattern much worse on
    the real PCB — the picture compressed horizontally to the left edge,
    colours rolled vertically. Symptom matches ringing on the DAC pins
    producing spurious sync edges the TV mis-reads.
    Drop drive strength back to the breadboard's 4 mA on both boards, but
    keep fast slew on v0.1 (the slow-slew setting was specifically there
2026-05-18 Pico: allow PIO clkdiv override for line-length compensation
    At clkdiv=2.0 the 912-sample PIO line takes 63.694 µs vs NTSC's
    spec 63.555 µs — 140 ns too long per scanline. Strict TVs re-trigger
    H-scan on each sync tip, so the picture shears diagonally by ~0.75
    NES pixels per line (about 70% of screen width over 240 lines).
    That matches exactly what the v0.1 PCB shows on a Sony Trinitron
    even with chroma disabled and audio unplugged.
2026-05-20 deploy: 2d5590d2a943157098fb58be29900382220fe404
2026-05-22 fix reset button logic
2026-05-23 deploy: 41b027654823d1af0a705b8c5231b4bae6f38ce6
2026-05-24 deploy: 0ba5a902fc1473e07c9a36db618b0a7dd76b1707
2026-05-24 Add .claude/ to .gitignore
    https://claude.ai/code/session_017RaW53URN8CTToM1DfCKjp
2026-05-24 Use 64 KB block erases for ~5x faster SD-to-flash copy
    Sector-by-sector 4 KB erase takes ~45 ms each (138s for 12 MB).
    The W25Q128 does 64 KB block erases in ~150 ms, covering the same
    range 16x faster. Full 12 MB erase drops from ~138s to ~29s.
    https://claude.ai/code/session_01M5y5ekZV6CoEoW4rCa5xtX
2026-05-24 HDMI: revert preamble back into the RAW block (green-screen layout)
    The separate RAW_REPEAT|8 preamble approach produced 642x506 (TV not
    entering HDMI mode). But the earlier build that packed preamble inside
    the HSTX_CMD_RAW block triggered HDMI mode detection (green screen =
    AVMUTE). Revert to that layout: the entire data island (preamble +
    guard + packets + guard) is emitted as one continuous HSTX_CMD_RAW|N
    stream.
2026-05-24 HDMI: fix GCP — replicate AVMUTE control across all 4 subpackets; set CD=8bpc
    The HDMI spec requires all 4 GCP subpackets to carry the same control
    data. Previously only subpacket 0 had CLEAR_AVMUTE; the other 3 were
    zeroed (= "no change"), which some sinks treat as "AVMUTE not cleared."
    This caused a green-screen (AVMUTE active) on TVs that majority-vote
    or require unanimous subpackets.
    Also set Color Depth = 4 (24 bits, 8 bpc) instead of 0 (not indicated)
2026-05-25 HDMI: source clk_hstx from pll_usb for clock-independent pixel timing
    The emulator needs clk_sys=315 MHz for performance, but HSTX needs
    exactly 125 MHz for a clean 25 MHz pixel clock. At 315 MHz sys, the
    integer clock divider can only produce 157.5 or 105 MHz — neither is
    125, so the ACR's CTS=25000 was wrong and the TV couldn't recover the
    audio sample clock.
    Fix: reconfigure pll_usb (unused since USB stdio is disabled on the
2026-05-25 Fix build: use shell.state instead of undeclared frame variable in diag
    https://claude.ai/code/session_01JVRuDRnPCYUqWG9F1UJBhv
2026-05-25 HDMI: fix stack overflow in init from 2 KB null_island temporary
    With 16 packets/line, null_island[524] = 2096 bytes on the stack.
    Combined with null_pkts[16] (496 bytes) and encode_packet locals,
    this overflows the default 4 KB Pico stack during video_hstx_init().
    Fix: emit NULL packets directly into the first audio line buffer
    and memcpy to the rest, eliminating the stack temporary entirely.
    https://claude.ai/code/session_01NnNgJmZqbf1WeNiJ97ZBnp
2026-05-25 Run HDMI audio test at 315 MHz sysclk
2026-05-25 Rotate HDMI silence packets on underrun
2026-05-25 Avoid HDMI scanout row write races
2026-05-26 Skip busy DMA channels in HSTX ISR to prevent cascade
    When both ping/pong channels complete between ISR invocations, the
    chain has already restarted one of them with stale config. Writing
    new read_addr/transfer_count to that running channel corrupts its
    active transfer, triggering immediate re-completion and a cascading
    4x frame-rate runaway (confirmed by dbl= counter rising ~100/sec).
    Fix: check dma_channel_is_busy() before reconfiguring. If the
2026-05-26 Add diagnostics for double-hit DMA buffer race investigation
    New fields in [hstx] log line:
    - race: count of times ISR rebuilt a buffer while its DMA channel was busy
    - 1stdbl: frame number of the first double-hit event
    - spinmax: worst-case spin lock wait time in µs (audio push contention)
    - printmax: worst-case printf duration in µs
    These isolate whether the 15-20s video+audio dropout is caused by
2026-05-29 final hue changes for now
2026-05-30 Add ISR ring buffer to capture cascade lead-up
    If the vsync padding doesn't fully prevent the cascade, the next thing
    we need is the sequence of events immediately before the first
    double-hit — that tells us whether the trigger is FIFO-related,
    audio-island-related, an emulator timing event, or something else
    entirely.
    Add a 32-entry circular buffer of per-ISR state:
2026-06-01 deploy: f89a9ea63e043716ecdc1c9a0cbd57ffaee1d678
